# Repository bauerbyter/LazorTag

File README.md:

LazorTag
========

--WORK IN PROGRESS--

A cheap open-source Arduino Lasertag system.

For more information see: https://github.com/bauerbyter/Lasertag/wiki

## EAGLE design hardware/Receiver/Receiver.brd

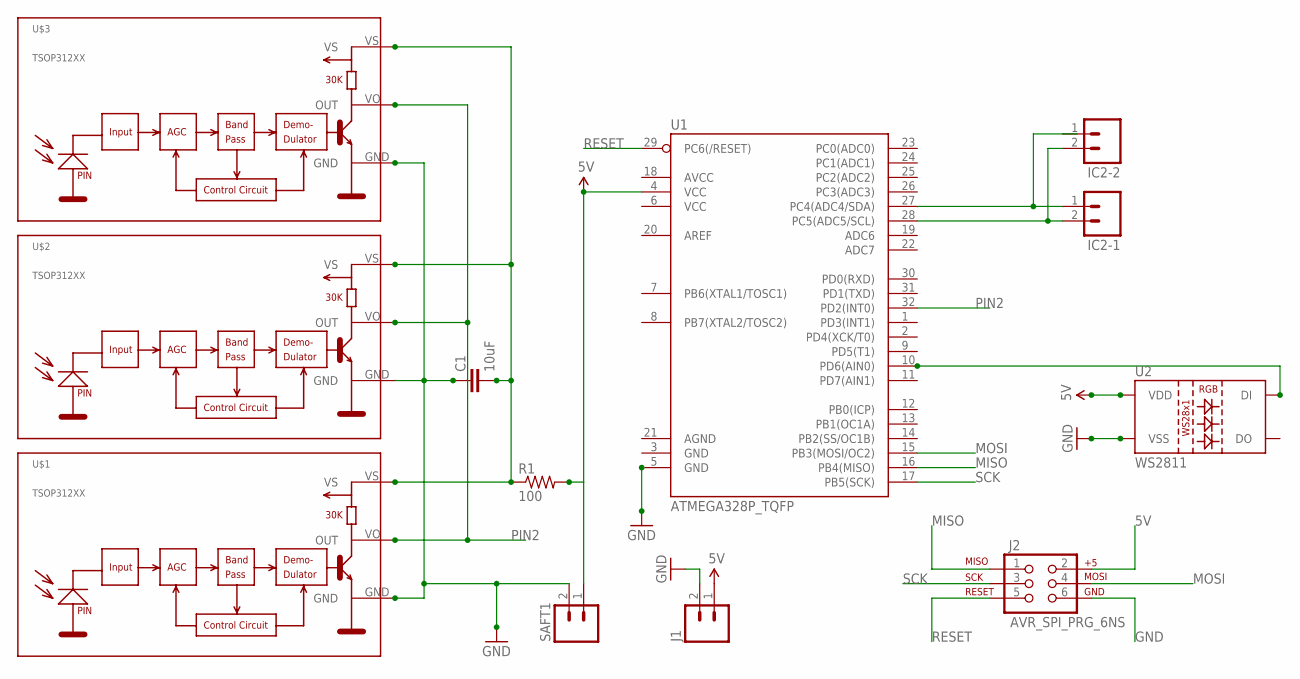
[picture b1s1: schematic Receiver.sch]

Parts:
C1: 10uF; 0603-CAP
IC2-1, IC2-2: M02-JST-2-PTH-NO_SILK; JST-2-PTH-NS
J1: M02-JST-2-PTH-NO_SILK; JST-2-PTH-NS
J2: AVR_SPI_PRG_6NS; 2X3-NS
R1: 100; 0603-RES
SAFT1: M02-JST-2-PTH-NO_SILK; JST-2-PTH-NS
U1: ATMEGA328P_TQFP; TQFP32-08
U2: WS2811; LED-TRICOLOR-5050-IC
U$1, U$2, U$3: TSOP312XX; TSOP312

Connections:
5V: J1.1, J2.2, R1.2, SAFT1.1, U1.4 (VCC), U2.3 (VDD), U2.5 (VDD)
GND: C1.1, J1.2, J2.6, SAFT1.2, U1.5 (GND), U2.6 (VSS), U$1.GND, U$2.GND, U$3.GND
MISO: J2.1, U1.16 (PB4(MISO))
MOSI: J2.4, U1.15 (PB3(MOSI/OC2))
unnamed: IC2-1.1, U1.27 (PC4(ADC4/SDA))
unnamed: C1.2, R1.1, U$1.VS, U$2.VS, U$3.VS
unnamed: IC2-1.2, IC2-2.2, U1.28 (PC5(ADC5/SCL))
unnamed: U1.10 (PD6(AIN0)), U2.2 (DI)
PIN2: U1.32 (PD2(INT0)), U$1.VO (OUT), U$2.VO (OUT), U$3.VO (OUT)
RESET: J2.5, U1.29 (PC6(/RESET))
SCK: J2.3, U1.17 (PB5(SCK))

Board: 2 copper layers, 12 parts (0 on the bottom side), 11 nets, no tracks yet.

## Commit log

2014-08-16 Add Folders and create empty arduino project
2014-08-16 Add sandbox project
    This project was just for testing, maybe some parts can recycled
2014-08-17 Add wiki link to readme
2014-12-25 Update README.md
    Change name to fancy: LazorTag
2015-08-06 Clean Up Folders
2015-08-06 First working Code for Sending IR and Receiving IR - not cleaned up yet
2015-08-06 moved arround the doubled files - sorry, still learning git :-)
2015-08-06 add .gitignore with sublime project and workspace files
2015-08-06 Sender: move Infrared Code for transmitting to own File
2015-08-06 Try out code formatter (SublimeAStyleFormatter) and reformat all code for better readability
2015-08-09 Sender: clean up and rename isFinished in isRunning
2015-08-10 Sender: Move activation of Interrupts in Setup
2015-08-10 Sender: Change from int to uint16_t
2015-08-10 Sender: move from cpp to c and resolve bug in sendind
2015-08-10 Receiver: move IRReceive to own C-File. Needs clean up
2015-08-12 add waffle.io badge
2015-08-12 Create LazorTag.h a global Headerfile for all and move some defines in it
2015-08-15 Receiver: Add Error Handling
2015-08-15 Add Timer to receiver and remove Error from sender. --TESTED
2015-08-15 move LazorTag.h to libraries folder
2015-08-15 Refactor IR in int
2015-08-15 rename folder
2015-08-19 add TWI Library
2015-09-10 add empty Master.ino
2015-11-18 Use PlatformIO and Atom to develop this crazy shit
2015-11-18 simple twi communication between Master and Receiver
2015-11-18 Working TWI connection between Master, Sender and Receiver. Now things get interesting
2015-11-19 Use new code layout
2016-03-09 no idea
2016-03-16 add Receiver Hardware
2016-03-16 create Sender schematic
2016-03-17 Remove old Files to clean up (yes I do this a lot :-) )

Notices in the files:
parts and their libraries:
SparkFun-DigitalIC: Licensing: Creative Commons ShareAlike 4.0 International - https://creativecommons.org/licenses/by-sa/4.0
